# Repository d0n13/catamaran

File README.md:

# Electric catamaran

Boat with two catamaran hulls with trusters driven by a joystick. Two ESC controllers driving the trusters and everything running on a rasspberry pi pico in micropython. Battery pack is a 5s12p pack driving the trusters. 1.2kw output. 21700 batteries

Hardware designed in [Fusion 360](https://gmail362014.autodesk360.com/g/projects/20220607531689401/data/dXJuOmFkc2sud2lwcHJvZDpmcy5mb2xkZXI6Y28uRkVOcG5FTk5Rc0s0LTh4UGM5VVRHdw)

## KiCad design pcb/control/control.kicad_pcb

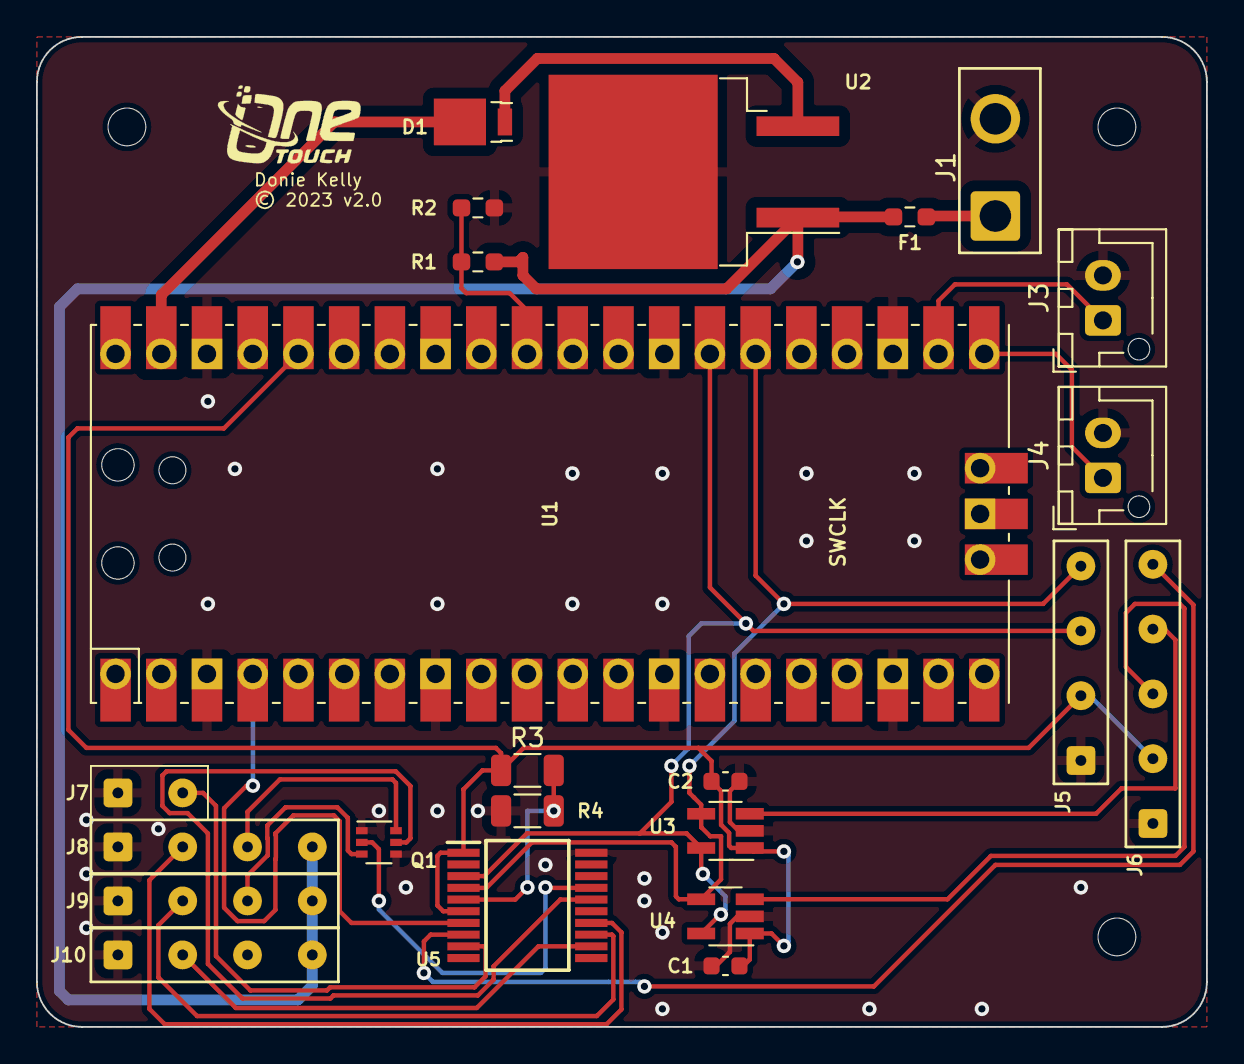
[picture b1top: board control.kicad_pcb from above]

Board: 2 copper layers, 65.0 x 55.0 mm, 27 parts (0 on the bottom side), 24 nets.

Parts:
C1, C2: 0.1µF; C_0603_1608Metric
D1: D_Schottky; DO220AA
F1: SMD Fuse; R_0603_1608Metric_Pad0.98x0.95mm_HandSolder
G1: LOGO; onetouchlogo
H1, H2, H3: MountingHole; MountingHole_2.1mm
J1: 24v; SolderWire-1sqmm_1x02_P5.4mm_D1.4mm_OD2.7mm
J3: ESC 1 PCM; JST_XH_B2B-XH-AM_1x02_P2.50mm_Vertical
J4: ESC 2 PCM; JST_XH_B2B-XH-AM_1x02_P2.50mm_Vertical
J5: OLED; SolderWire-0.1sqmm_1x04_P3.6mm_D0.4mm_OD1mm
J6: Joystick; SolderWire-0.1sqmm_1x05_P3.6mm_D0.4mm_OD1mm
J7: Cutout; SolderWire-0.1sqmm_1x02_P3.6mm_D0.4mm_OD1mm
J8: Switch 1; SolderWire-0.1sqmm_1x04_P3.6mm_D0.4mm_OD1mm
J9: Switch 2; SolderWire-0.1sqmm_1x04_P3.6mm_D0.4mm_OD1mm
J10: Switch 3; SolderWire-0.1sqmm_1x04_P3.6mm_D0.4mm_OD1mm
Q1: US6K1; SOT-363_SC-70-6
R1: 100k; R_0603_1608Metric_Pad0.98x0.95mm_HandSolder
R2: 18K; R_0603_1608Metric_Pad0.98x0.95mm_HandSolder
R3: 1K; R_1206_3216Metric
R4: 15K; R_1206_3216Metric
U1: Pico; RPi_Pico_SMD_TH
U2: L7805; TO-263-2
U3, U4: MCP3021; SOT-23-5_HandSoldering
U5: MCP23009-E_SS; SOP65P780X200-20N

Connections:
+3V3: C1.1, C2.1, J5.2, J6.2, R3.1, U1.36 (3V3), U3.1 (VCC), U4.1 (VCC), U5.1 (VDD), U5.6 (~RESET)
+24V: F1.2, J8.4, J9.4, J10.4, R1.1, U2.1 (IN)
+BATT: F1.1, J1.1
GND: C1.2, C2.2, J1.2, J3.2, J4.2, J5.1, J6.1, J7.1, J8.1, J9.1, J10.1, Q1.1 (S), Q1.4 (S), R2.2, R4.2, U1.3 (GND), U1.8 (GND), U1.13 (GND), U1.18 (GND), U1.23 (GND), U1.28 (GND), U1.38 (GND), U2.2 (GND), U3.2 (GND), U4.2 (GND), U5.20 (VSS)
unnamed: D1.1 (K), U1.39 (VSYS)
unnamed: D1.2 (A), U2.3 (OUT)
unnamed: J3.1, U1.22 (GPIO17)
unnamed: J4.1, U1.21 (GPIO16)
unnamed: J6.3, U3.3 (AIN)
unnamed: J6.4, U4.3 (AIN)
unnamed: J6.5, U5.8 (GP0)
unnamed: J7.2, U5.9 (GP1)
unnamed: J8.2, U5.14 (GP4)
unnamed: J8.3, Q1.6 (D)
unnamed: J9.2, U5.13 (GP3)
unnamed: J9.3, Q1.3 (D)
unnamed: J10.2, U5.12 (GP2)
unnamed: Q1.2 (G), U5.17 (GP7)
unnamed: Q1.5 (G), U5.16 (GP6)
unnamed: R1.2, R2.1, U1.31 (GPIO26_ADC0)
unnamed: R3.2, R4.1, U5.5 (ADDR)
unnamed: U1.4 (GPIO2), U5.7 (INT)
SCL: J5.3, U1.27 (GPIO21), U3.5 (SCL), U4.5 (SCL), U5.3 (SCL)
SDA: J5.4, U1.26 (GPIO20), U3.4 (SDA), U4.4 (SDA), U5.4 (SDA)

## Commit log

2022-06-10 Initial version
2022-06-10 Updated comments
2022-06-10 Updated comment
2022-06-12 Added docs
2022-06-12 Added more inputs and controls
2022-06-12 Map joystick axis to servos and motors. Clean up code
2022-06-13 Added master arm and steering mod
2022-06-27 Added .gitignore
2022-06-27 Updated comment for speed controller
2022-07-05 Created PCB design
2022-07-08 Updated pcb
2022-07-24 v2 of design
2023-05-20 Updated pcb and code
2023-05-23 Version 2.0 sent to manafacture
2023-07-18 Updated code
2023-07-24 library code update
2023-07-26 Update to create more classes for readability
2023-07-26 Clean up code
2023-07-28 Fixed joystick mapping code
2023-07-28 Clean up code and refactor
2023-07-28 Add files via upload
    boat render (right hull)
2023-07-28 Update README.md
    Added images
2023-07-28 Removed
2023-07-28 Update README.md
    Added image of pcb
2023-07-28 Update README.md
    updated description

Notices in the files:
pcb/control/control.kicad_pcb:
© 2023 v2.0
